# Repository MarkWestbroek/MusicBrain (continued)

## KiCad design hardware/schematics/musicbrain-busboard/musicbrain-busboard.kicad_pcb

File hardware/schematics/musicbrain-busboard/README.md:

# MusicBrain busboard — Teensy 4.1-backplane (rev 3.1, gen 2)

**Praktisch:** dit is de ruggengraat van het systeem. Eén Teensy 4.1
bestuurt alle functiekaarten die je in de zes slots prikt; het bord
verzorgt voeding, de SPI-bus, MIDI (2 in / 2 uit), USB-host, CAN, het
display en de gedeelde audio-lijnen. Hier begint elke MusicBrain-bouw.

**Status**: rev 3.1 AF — ERC 0, netlijst pad-voor-pad geverifieerd, **DRC 0/0**;
koper volledig via de freerouting-pijplijn (`--route-gnd`). Fab-pakket in
`fab/`. **Bestelbaar.**
**Plannen**: `doc/busboard-v3-plan.md` (v3-delta's) + `doc/busboard-v2-plan.md`
(architectuur/pintabellen) + `doc/spi-bus-spec.md` v2.0 (leidend voor de bus).

## Wat is v3 (gen 2)

- **Bord 203,2 × 128,5 mm (40 HP × 3U-paneelvlak)** — paneel, fronts en
  grondbord delen één footprint en gatenraster (M3: 4 hoeken + noord/zuid-
  midden) → zelfstandige unit mogelijk.
- **6 slots 2×12** (was 2×10), gecentreerd op het bordhart, steek 20,32 mm
  (4 HP). Slot-pinout per spi-bus-spec v2.0: pin 19 = CONVST, 20 = GND-guard,
  21–24 = MCLK/BCLK/LRCLK/I2SD·slot.
- **Audio over de bus**: klokrails gedeeld (zelfde netten als Teensy-I2S1 en
  de codec-header — klokmaster is een firmwarekeuze), één datalijn per slot.
- **J24 audiohub** (2×7, oostrand naast de hubs, búiten het kaartvolume):
  klokken + I2SD1–6 verzameld voor een toekomstige FPGA-/TDM-mixer; een
  expander-segment krijgt zijn klokken via zijn eigen J24 aangeleverd.
- **MIDI 2× IN / 2× UIT**: J22 (OUT2 = TX7/pin 29) met eigen 74LVC1G17 (U14).
- **J23 USB-host-doorvoer** (2×5): rij A = kabeltje van de Teensy-hostpads,
  rij B = kabeltje naar de paneel-USB-A; pin-voor-pin doorverbonden en
  volgorde-ongevoelig. VBUS loopt via VIN = de +5V-rail → daarom U2 nu
  **R-78E5.0-1.0** (1 A).
- **J25 Axon-voeding** (1×2, rev 3.1): +5V/GND naast J19, voedt de
  Axon-netbridge (ESP32-sidecar aan DLG1 — `doc/axon-plan.md`). Pin 1
  landt op het +5V-spoor van de voedingsbundel.

## Blokken (architectuur = v2)

- **Teensy 4.1** (west, op 2× 1×24 socketstrip; SMD ≤ 6 mm eronder mag).
- **6 slots** (J1–J6, 2×12) + **2 hubs** (J7/J8, 2×5 IDC, pinout = v1).
- **74HC154-CS-decoder** (U4, noordstrook): CSA0–3 + /E → 16 geografische CS.
- **IRQ-keten**: 2× 74HC165 (U5 zuidwest: IRQ1–6; U6 noordoost: IRQ7–12,
  uitlezen via decoder-Y14/IRQSTAT; per chip een PL-RC).
- **Expansie**: 74LVC245-buffer (U8) + J21 (2×13 IDC) voor één
  expander-segment (CS9–14, IRQ7–12; XRST-lijn = reserve sinds gen 2).
- **MIDI**: 2× IN (H11L1-opto's U9/U10) + 2× UIT (74LVC1G17 U11/U14).
- **CAN3**: SN65HVD230 (U12, zuidoost) + JP1-terminator + J16 (+12V mee).
- **Codec-poort** (J17, 2×7): I2S1 + CODEC_RST; I²C via de Qwiic-keten (J12).
- **TUNE-IN** (J18 + klem/deler → pin 1), **DLG-UART's** (J19/J20, Serial3/4).
- Voeding: J9 (2×5 IDC, 10-pins Eurorack: alleen ±12V/GND) → R-78E5.0-1.0
  (U2) → 5 V; AMS1117 (U3) → 3V3; ontkoppelbank C1–C8.

## Werkwijze koper

`gen_bus3_sch.py` + `gen_bus3_pcb.py` (placement + SES native inlezen).
Pijplijn: DSN-export via de KiCad-MCP-server → `prep_dsn.py --route-gnd`
(GND blijft routeerbaar net: de router respecteert dan de GND-pads én maakt
het net zelf af; de kopervlakken zijn bonus) → Docker-freerouting best-of-N →
netcheck + DRC 0/0 als poortwachters. `BUS3_NOROUTE=1` geeft het kale
placement-bord voor de DSN-export.

## Aansluitoverzicht

### Pinouts

Bovenaanzicht van het bord (kijkend op de pinnen); pin 1 = vierkant.
Gegenereerd uit het bordbestand met `hardware/kicad-generators/pinout_svg.py`.

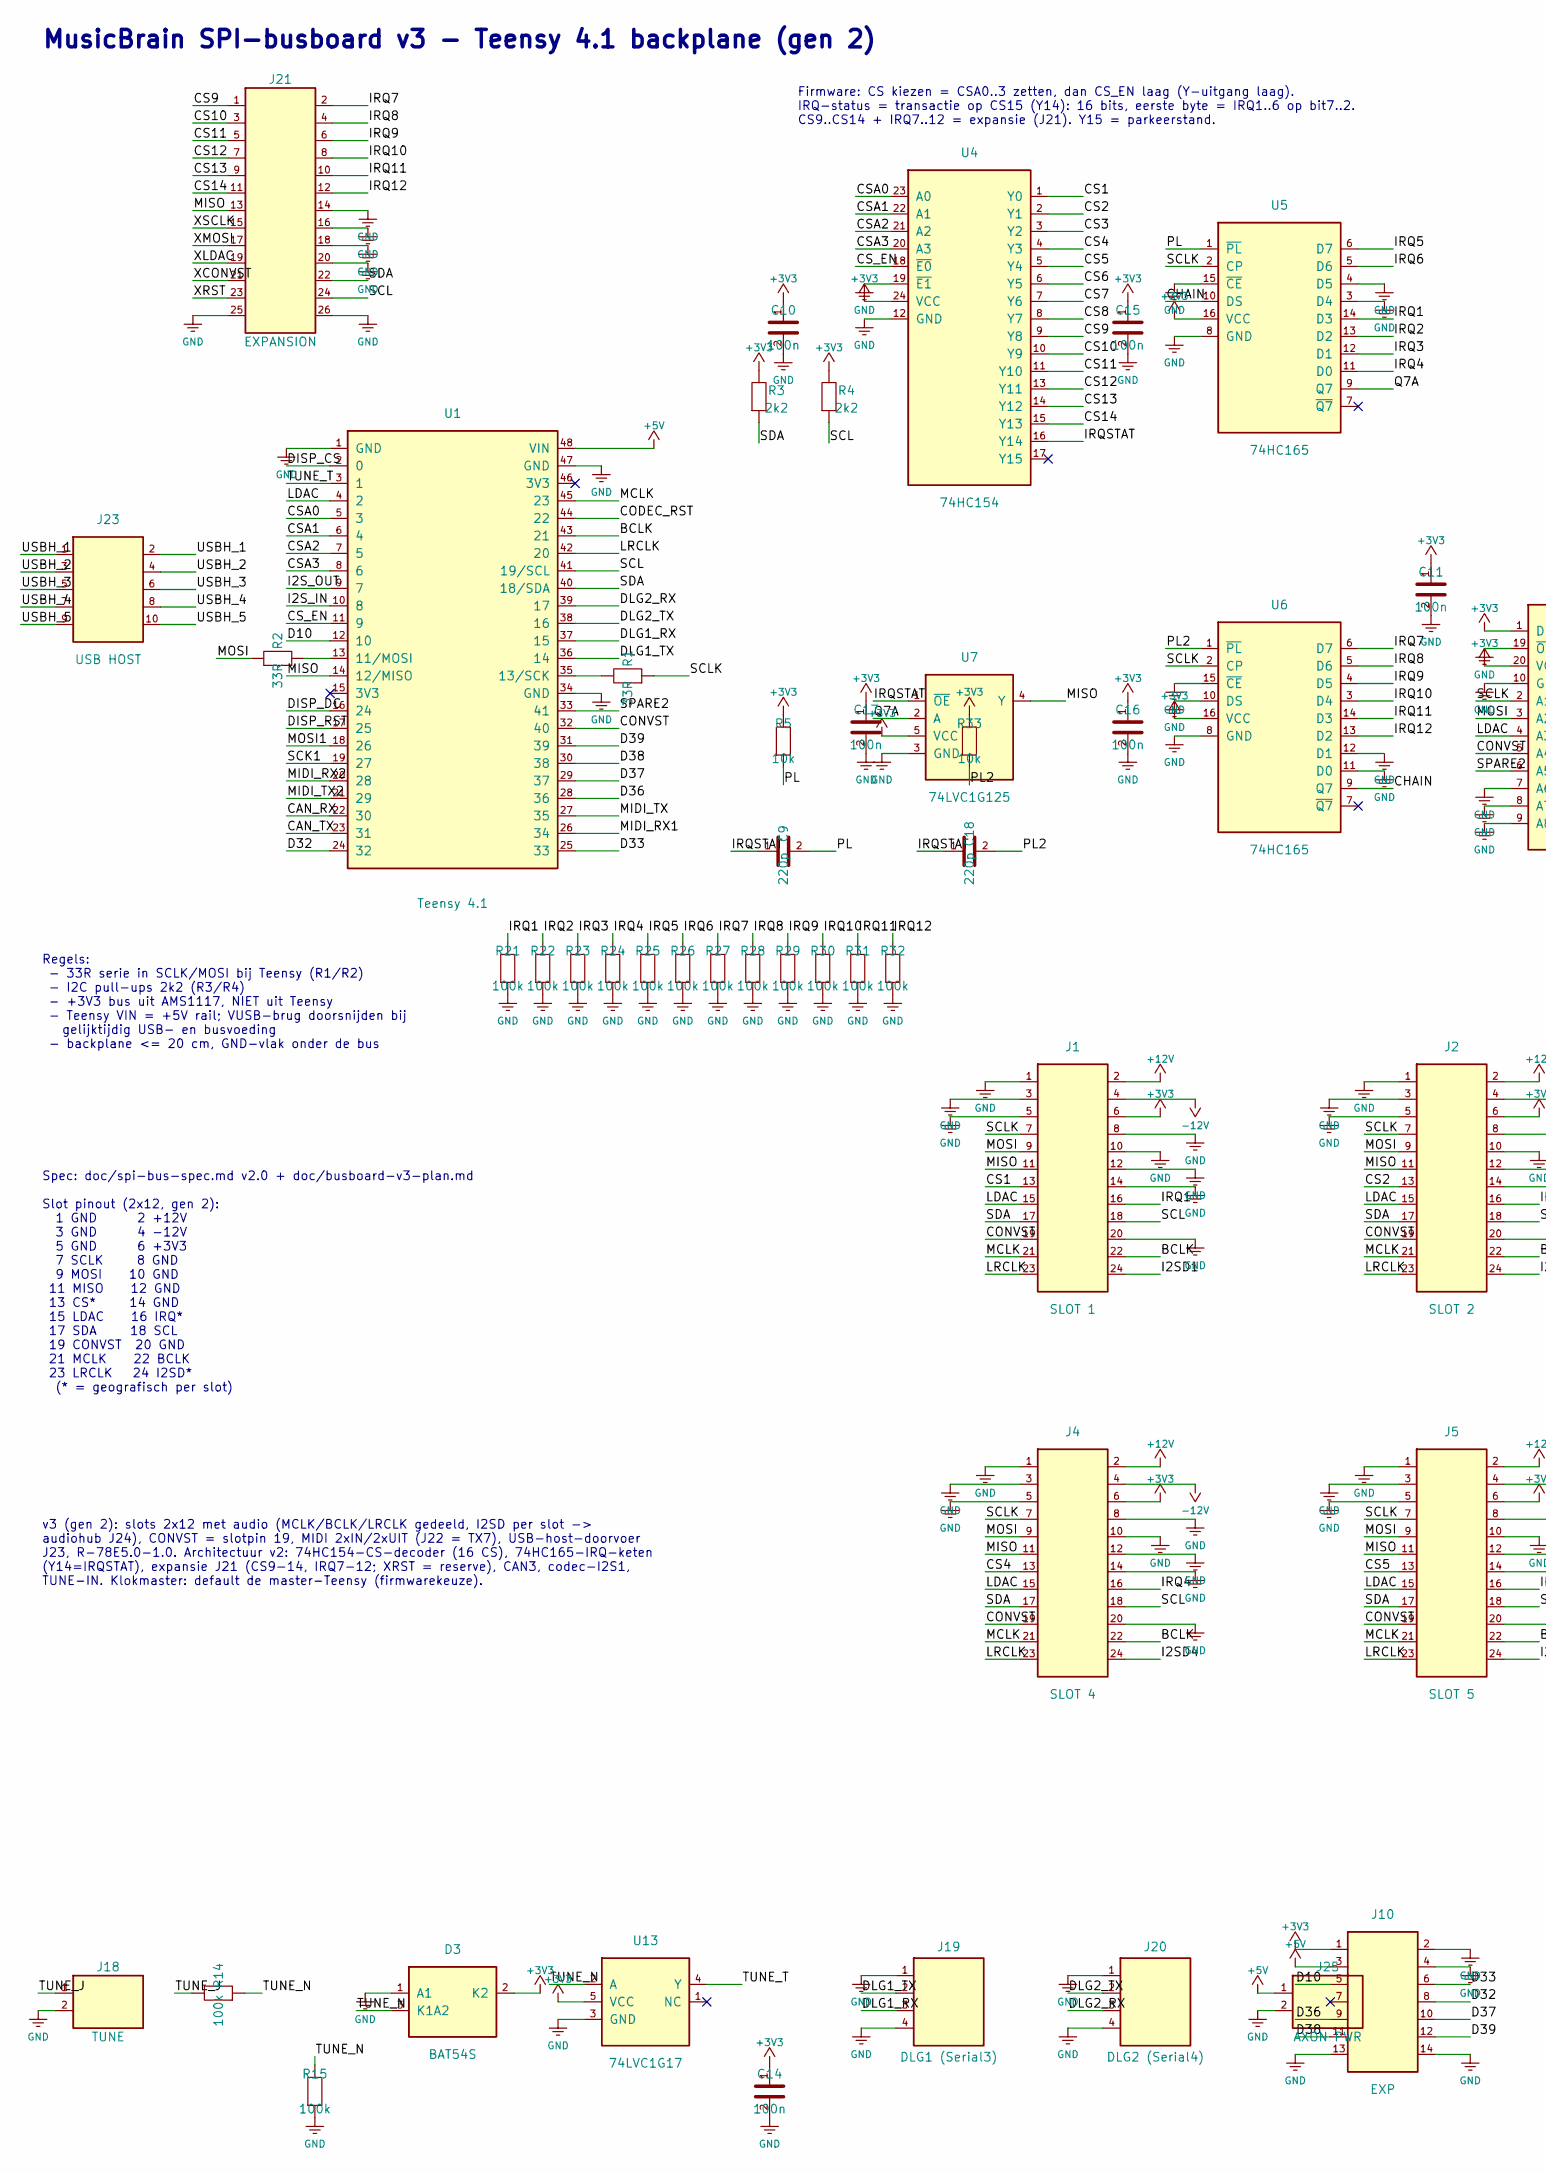
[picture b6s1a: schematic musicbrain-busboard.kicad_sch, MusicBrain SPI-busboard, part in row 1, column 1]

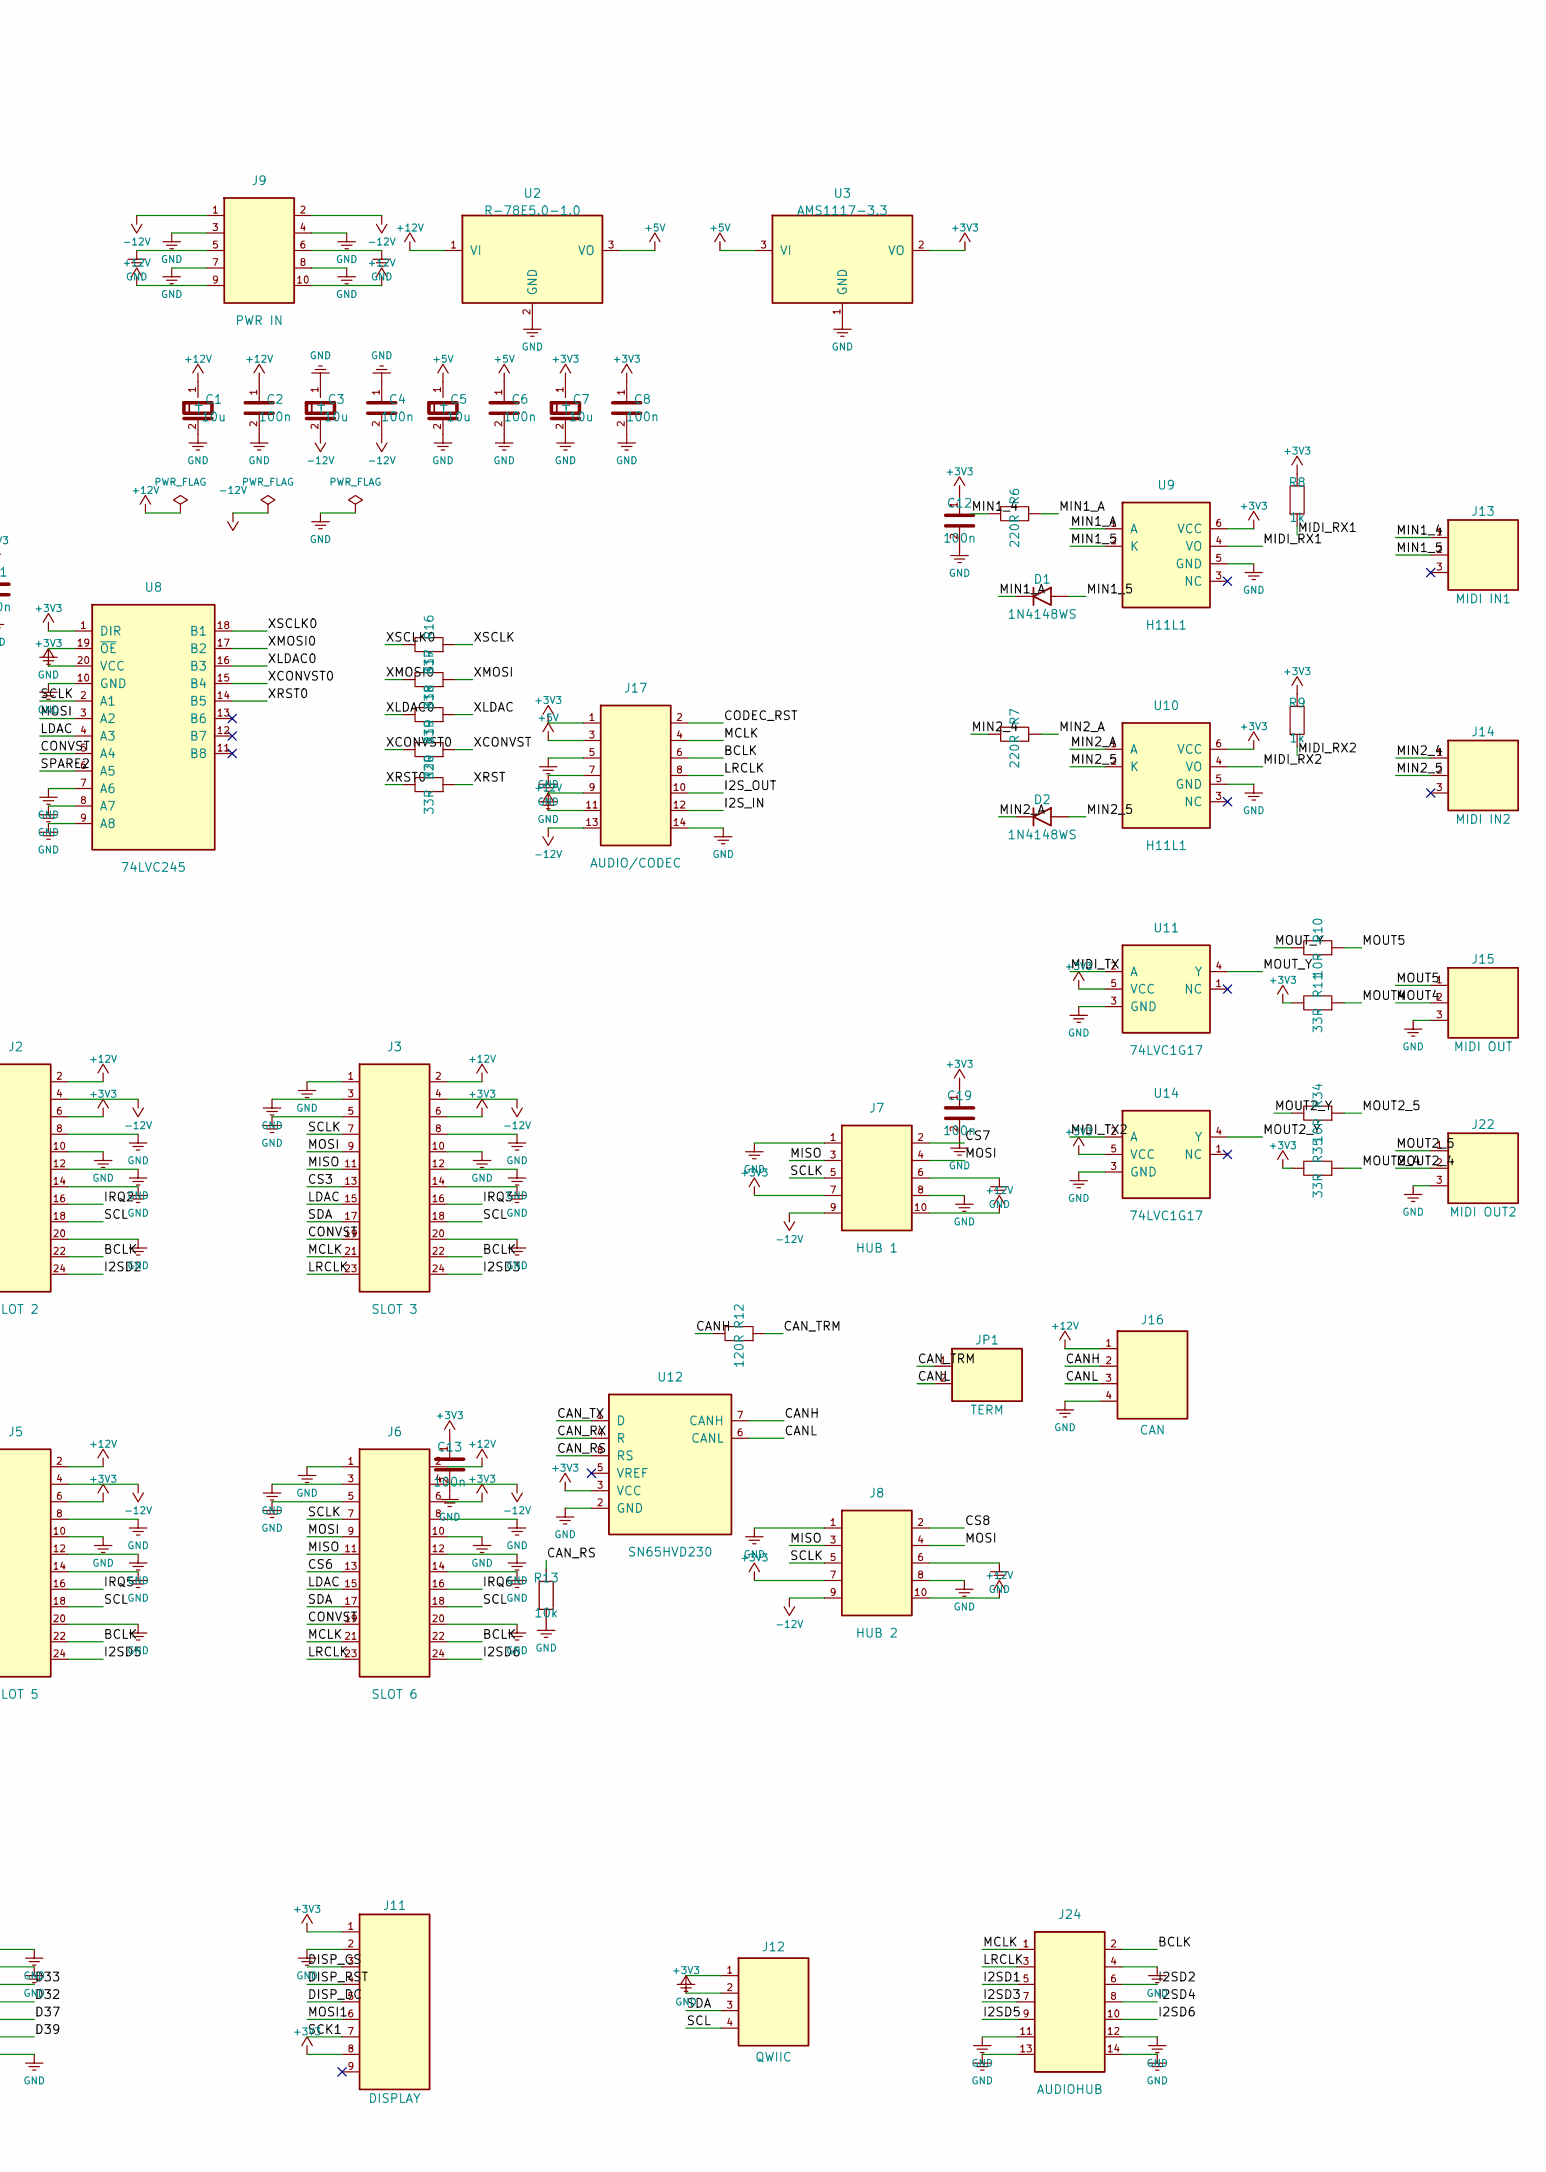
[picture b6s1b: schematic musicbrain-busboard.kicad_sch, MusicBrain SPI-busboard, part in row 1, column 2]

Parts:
C1, C3, C5, C7: 10u; CP_Elec_4x5.3
C2, C4, C6, C8, C10, C11, C12, C13, C14, C15, C16, C17, C19: 100n; C_0805_2012Metric
C9, C18: 220p; C_0805_2012Metric
D1, D2: 1N4148WS; D_SOD-323
D3: BAT54S; SOT-23
J1: SLOT 1; PinSocket_2x12_P2.54mm_Vertical
J2: SLOT 2; PinSocket_2x12_P2.54mm_Vertical
J3: SLOT 3; PinSocket_2x12_P2.54mm_Vertical
J4: SLOT 4; PinSocket_2x12_P2.54mm_Vertical
J5: SLOT 5; PinSocket_2x12_P2.54mm_Vertical
J6: SLOT 6; PinSocket_2x12_P2.54mm_Vertical
J7: HUB 1; IDC-Header_2x05_P2.54mm_Vertical
J8: HUB 2; IDC-Header_2x05_P2.54mm_Vertical
J9: PWR IN; IDC-Header_2x05_P2.54mm_Vertical
J10: EXP; PinHeader_2x07_P2.54mm_Vertical
J11: DISPLAY; PinHeader_1x09_P2.54mm_Vertical
J12: QWIIC; PinHeader_1x04_P2.54mm_Vertical
J13: MIDI IN1; PinHeader_1x03_P2.54mm_Vertical
J14: MIDI IN2; PinHeader_1x03_P2.54mm_Vertical
J15: MIDI OUT; PinHeader_1x03_P2.54mm_Vertical
J16: CAN; PinHeader_1x04_P2.54mm_Vertical
J17: AUDIO/CODEC; PinHeader_2x07_P2.54mm_Vertical
J18: TUNE; PinHeader_1x02_P2.54mm_Vertical
J19: DLG1 (Serial3); PinHeader_1x04_P2.54mm_Vertical
J20: DLG2 (Serial4); PinHeader_1x04_P2.54mm_Vertical
J21: EXPANSION; IDC-Header_2x13_P2.54mm_Vertical
J22: MIDI OUT2; PinHeader_1x03_P2.54mm_Vertical
J23: USB HOST; PinHeader_2x05_P2.54mm_Vertical
J24: AUDIOHUB; PinHeader_2x07_P2.54mm_Vertical
J25: AXON PWR; PinHeader_1x02_P2.54mm_Vertical
JP1: TERM; SolderJumper-2_P1.3mm_Open_TrianglePad1.0x1.5mm
R1, R2, R11, R16, R17, R18, R19, R20, R35: 33R; R_0805_2012Metric
R3, R4: 2k2; R_0805_2012Metric
R5, R13, R33: 10k; R_0805_2012Metric
R6, R7: 220R; R_0805_2012Metric
R8, R9: 1k; R_0805_2012Metric
R10, R34: 10R; R_0805_2012Metric
R12: 120R; R_0805_2012Metric
R14, R15, R21, R22, R23, R24, R25, R26, R27, R28, R29, R30, R31, R32: 100k; R_0805_2012Metric
U1: Teensy 4.1
U2: R-78E5.0-1.0; Converter_DCDC_RECOM_R-78E-0.5_THT
U3: AMS1117-3.3; SOT-223-3_TabPin2
U4: 74HC154; SOIC-24W_7.5x15.4mm_P1.27mm
U5, U6: 74HC165; SOIC-16_3.9x9.9mm_P1.27mm
U7: 74LVC1G125; SOT-23-5
U8: 74LVC245; SOIC-20W_7.5x12.8mm_P1.27mm
U9, U10: H11L1; DIP-6_W7.62mm
U11, U13, U14: 74LVC1G17; SOT-23-5
U12: SN65HVD230; SOIC-8_3.9x4.9mm_P1.27mm

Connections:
+3V3: C7.1 (+), C8.1, C10.1, C11.1, C12.1, C13.1, C14.1, C15.1, C16.1, C17.1, C19.1, D3.2 (K2), J1.6, J2.6, J3.6, J4.6, J5.6, J6.6, J7.7, J8.7, J10.1, J11.1, J11.8, J12.2, J17.1, R3.1, R4.1, R5.1, R8.1, R9.1, R11.1, R33.1, R35.1, U3.2 (VO), U4.24 (VCC), U5.16 (VCC), U6.16 (VCC), U7.5 (VCC), U8.1 (DIR), U8.20 (VCC), U9.6 (VCC), U10.6 (VCC), U11.5 (VCC), U12.3 (VCC), U13.5 (VCC), U14.5 (VCC)
+5V: C5.1 (+), C6.1, J10.3, J17.3, J25.1, U1.48 (VIN), U2.3 (VO), U3.3 (VI)
+12V: C1.1 (+), C2.1, J1.2, J2.2, J3.2, J4.2, J5.2, J6.2, J7.10, J8.10, J9.9, J9.10, J16.1, J17.11, U2.1 (VI)
-12V: C3.2 (-), C4.2, J1.4, J2.4, J3.4, J4.4, J5.4, J6.4, J7.9, J8.9, J9.1, J9.2, J17.13
/BCLK: J1.22, J2.22, J3.22, J4.22, J5.22, J6.22, J17.6, J24.2, U1.43 (21)
/CANH: J16.2, R12.1, U12.7 (CANH)
/CANL: J16.3, JP1.2, U12.6 (CANL)
/CAN_RS: R13.1, U12.8 (RS)
/CAN_RX: U1.22 (30), U12.4 (R)
/CAN_TRM: JP1.1, R12.2
/CAN_TX: U1.23 (31), U12.1 (D)
/CHAIN: U5.10 (DS), U6.9 (Q7)
/CODEC_RST: J17.2, U1.44 (22)
/CONVST: J1.19, J2.19, J3.19, J4.19, J5.19, J6.19, U1.32 (40), U8.5 (A4)
/CS1: J1.13, U4.1 (Y0)
/CS2: J2.13, U4.2 (Y1)
/CS3: J3.13, U4.3 (Y2)
/CS4: J4.13, U4.4 (Y3)
/CS5: J5.13, U4.5 (Y4)
/CS6: J6.13, U4.6 (Y5)
/CS7: J7.2, U4.7 (Y6)
/CS8: J8.2, U4.8 (Y7)
/CS9: J21.1, U4.9 (Y8)
/CS10: J21.3, U4.10 (Y9)
/CS11: J21.5, U4.11 (Y10)
/CS12: J21.7, U4.13 (Y11)
/CS13: J21.9, U4.14 (Y12)
/CS14: J21.11, U4.15 (Y13)
/CSA0: U1.5 (3), U4.23 (A0)
/CSA1: U1.6 (4), U4.22 (A1)
/CSA2: U1.7 (5), U4.21 (A2)
/CSA3: U1.8 (6), U4.20 (A3)
/CS_EN: U1.11 (9), U4.18 (~E0)
/D10: J10.5, U1.12 (10)
/D32: J10.8, U1.24 (32)
/D33: J10.6, U1.25 (33)
/D36: J10.9, U1.28 (36)
/D37: J10.10, U1.29 (37)
/D38: J10.11, U1.30 (38)
/D39: J10.12, U1.31 (39)
/DISP_CS: J11.3, U1.2 (0)
/DISP_DC: J11.5, U1.16 (24)
/DISP_RST: J11.4, U1.17 (25)
/DLG1_RX: J19.3, U1.37 (15)
/DLG1_TX: J19.2, U1.36 (14)
/DLG2_RX: J20.3, U1.39 (17)
/DLG2_TX: J20.2, U1.38 (16)
/I2SD1: J1.24, J24.5
/I2SD2: J2.24, J24.6
/I2SD3: J3.24, J24.7
/I2SD4: J4.24, J24.8
/I2SD5: J5.24, J24.9
/I2SD6: J6.24, J24.10
/I2S_IN: J17.12, U1.10 (8)
/I2S_OUT: J17.10, U1.9 (7)
/IRQ1: J1.16, R21.1, U5.14 (D3)
/IRQ2: J2.16, R22.1, U5.13 (D2)
/IRQ3: J3.16, R23.1, U5.12 (D1)
/IRQ4: J4.16, R24.1, U5.11 (D0)
/IRQ5: J5.16, R25.1, U5.6 (D7)
/IRQ6: J6.16, R26.1, U5.5 (D6)
/IRQ7: J21.2, R27.1, U6.6 (D7)
/IRQ8: J21.4, R28.1, U6.5 (D6)
/IRQ9: J21.6, R29.1, U6.4 (D5)
/IRQ10: J21.8, R30.1, U6.3 (D4)
/IRQ11: J21.10, R31.1, U6.14 (D3)
/IRQ12: J21.12, R32.1, U6.13 (D2)
/IRQSTAT: C9.1, C18.1, U4.16 (Y14), U7.1 (~OE)
/LDAC: J1.15, J2.15, J3.15, J4.15, J5.15, J6.15, U1.4 (2), U8.4 (A3)
/LRCLK: J1.23, J2.23, J3.23, J4.23, J5.23, J6.23, J17.8, J24.3, U1.42 (20)
/MCLK: J1.21, J2.21, J3.21, J4.21, J5.21, J6.21, J17.4, J24.1, U1.45 (23)
/MIDI_RX1: R8.2, U1.26 (34), U9.4 (VO)
/MIDI_RX2: R9.2, U1.20 (28), U10.4 (VO)
/MIDI_TX: U1.27 (35), U11.2 (A)
/MIDI_TX2: U1.21 (29), U14.2 (A)
/MIN1_4: J13.1, R6.1
/MIN1_5: D1.2 (A), J13.2, U9.2 (K)
/MIN1_A: D1.1 (K), R6.2, U9.1 (A)
/MIN2_4: J14.1, R7.1
/MIN2_5: D2.2 (A), J14.2, U10.2 (K)
/MIN2_A: D2.1 (K), R7.2, U10.1 (A)
/MISO: J1.11, J2.11, J3.11, J4.11, J5.11, J6.11, J7.3, J8.3, J21.13, U1.14 (12/MISO), U7.4 (Y)
/MOSI: J1.9, J2.9, J3.9, J4.9, J5.9, J6.9, J7.4, J8.4, R2.1, U8.3 (A2)
/MOSI1: J11.6, U1.18 (26)
/MOUT2_4: J22.2, R35.2
/MOUT2_5: J22.1, R34.2
/MOUT2_Y: R34.1, U14.4 (Y)
/MOUT4: J15.2, R11.2
/MOUT5: J15.1, R10.2
/MOUT_Y: R10.1, U11.4 (Y)
/PL: C9.2, R5.2, U5.1 (~PL)
/PL2: C18.2, R33.2, U6.1 (~PL)
/Q7A: U5.9 (Q7), U7.2 (A)
/SCK1: J11.7, U1.19 (27)
/SCL: J1.18, J2.18, J3.18, J4.18, J5.18, J6.18, J12.4, J21.24, R4.2, U1.41 (19/SCL)
/SCLK: J1.7, J2.7, J3.7, J4.7, J5.7, J6.7, J7.5, J8.5, R1.2, U5.2 (CP), U6.2 (CP), U8.2 (A1)
/SDA: J1.17, J2.17, J3.17, J4.17, J5.17, J6.17, J12.3, J21.22, R3.2, U1.40 (18/SDA)
/SPARE2: U1.33 (41), U8.6 (A5)
/TUNE_J: J18.1, R14.1
/TUNE_N: D3.3 (K1A2), R14.2, R15.1, U13.2 (A)
/TUNE_T: U1.3 (1), U13.4 (Y)
/USBH_1: J23.1, J23.2
/USBH_2: J23.3, J23.4
/USBH_3: J23.5, J23.6
/USBH_4: J23.7, J23.8
/USBH_5: J23.9, J23.10
/XCONVST: J21.21, R19.2
/XCONVST0: R19.1, U8.15 (B4)
/XLDAC: J21.19, R18.2
/XLDAC0: R18.1, U8.16 (B3)
/XMOSI: J21.17, R17.2
/XMOSI0: R17.1, U8.17 (B2)
/XRST: J21.23, R20.2
/XRST0: R20.1, U8.14 (B5)
/XSCLK: J21.15, R16.2
/XSCLK0: R16.1, U8.18 (B1)
GND: C1.2 (-), C2.2, C3.1 (+), C4.1, C5.2 (-), C6.2, C7.2 (-), C8.2, C10.2, C11.2, C12.2, C13.2, C14.2, C15.2, C16.2, C17.2, C19.2, D3.1 (A1), J1.1, J1.3, J1.5, J1.8, J1.10, J1.12, J1.14, J1.20, J2.1, J2.3, J2.5, J2.8, J2.10, J2.12, J2.14, J2.20, J3.1, J3.3, J3.5, J3.8, J3.10, J3.12, J3.14, J3.20, J4.1, J4.3, J4.5, J4.8, J4.10, J4.12, J4.14, J4.20, J5.1, J5.3, J5.5, J5.8, J5.10, J5.12, J5.14, J5.20, J6.1, J6.3, J6.5, J6.8, J6.10, J6.12, J6.14, J6.20, J7.1, J7.6, J7.8, J8.1, J8.6, J8.8, J9.3, J9.4, J9.5, J9.6, J9.7, J9.8, J10.2, J10.4, J10.13, J10.14, J11.2, J12.1, J15.3, J16.4, J17.5, J17.7, J17.9, J17.14, J18.2, J19.1, J19.4, J20.1, J20.4, J21.14, J21.16, J21.18, J21.20, J21.25, J21.26, J22.3, J24.4, J24.11, J24.12, J24.13, J24.14, J25.2, R13.2, R15.2, R21.2, R22.2, R23.2, R24.2, R25.2, R26.2, R27.2, R28.2, R29.2, R30.2, R31.2, R32.2, U1.1 (GND), U1.34 (GND), U1.47 (GND), U2.2 (GND), U3.1 (GND), U4.12 (GND), U4.19 (~E1), U5.3 (D4), U5.4 (D5), U5.8 (GND), U5.15 (~CE), U6.8 (GND), U6.10 (DS), U6.11 (D0), U6.12 (D1), U6.15 (~CE), U7.3 (GND), U8.7 (A6), U8.8 (A7), U8.9 (A8), U8.10 (GND), U8.19 (~OE), U9.5 (GND), U10.5 (GND), U11.3 (GND), U12.2 (GND), U13.3 (GND), U14.3 (GND)
unnamed: R2.2, U1.13 (11/MOSI)
unnamed: R1.1, U1.35 (13/SCK)

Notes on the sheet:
MusicBrain SPI-busboard v3 - Teensy 4.1 backplane (gen 2)
v3 (gen 2): slots 2x12 met audio (MCLK/BCLK/LRCLK gedeeld, I2SD per slot -> audiohub J24), CONVST = slotpin 19, MIDI 2xIN/2xUIT (J22 = TX7), USB-host-doorvoer J23, R-78E5.0-1.0. Architectuur v2: 74HC154-CS-decoder (16 CS), 74HC165-IRQ-keten (Y14=IRQSTAT), expansie J21 (CS9-14, IRQ7-12; XRST = reser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
Spec: doc/spi-bus-spec.md v2.0 + doc/busboard-v3-plan.md Slot pinout (2x12, gen 2): 1 GND 2 +12V 3 GND 4 -12V 5 GND 6 +3V3 7 SCLK 8 GND 9 MOSI 10 GND 11 MISO 12 GND 13 CS* 14 GND 15 LDAC 16 IRQ* 17 SDA 18 SCL 19 CONVST 20 GND 21 MCLK 22 BCLK 23 LRCLK 24 I2SD* (* = geografisch per slot)
Regels: - 33R serie in SCLK/MOSI bij Teensy (R1/R2) - I2C pull-ups 2k2 (R3/R4) - +3V3 bus uit AMS1117, NIET uit Teensy - Teensy VIN = +5V rail; VUSB-brug doorsnijden bij gelijktijdig USB- en busvoeding - backplane <= 20 cm, GND-vlak onder de bus
Firmware: CS kiezen = CSA0..3 zetten, dan CS_EN laag (Y-uitgang laag). IRQ-status = transactie op CS15 (Y14): 16 bits, eerste byte = IRQ1..6 op bit7..2. CS9..CS14 + IRQ7..12 = expansie (J21). Y15 = parkeerstand.

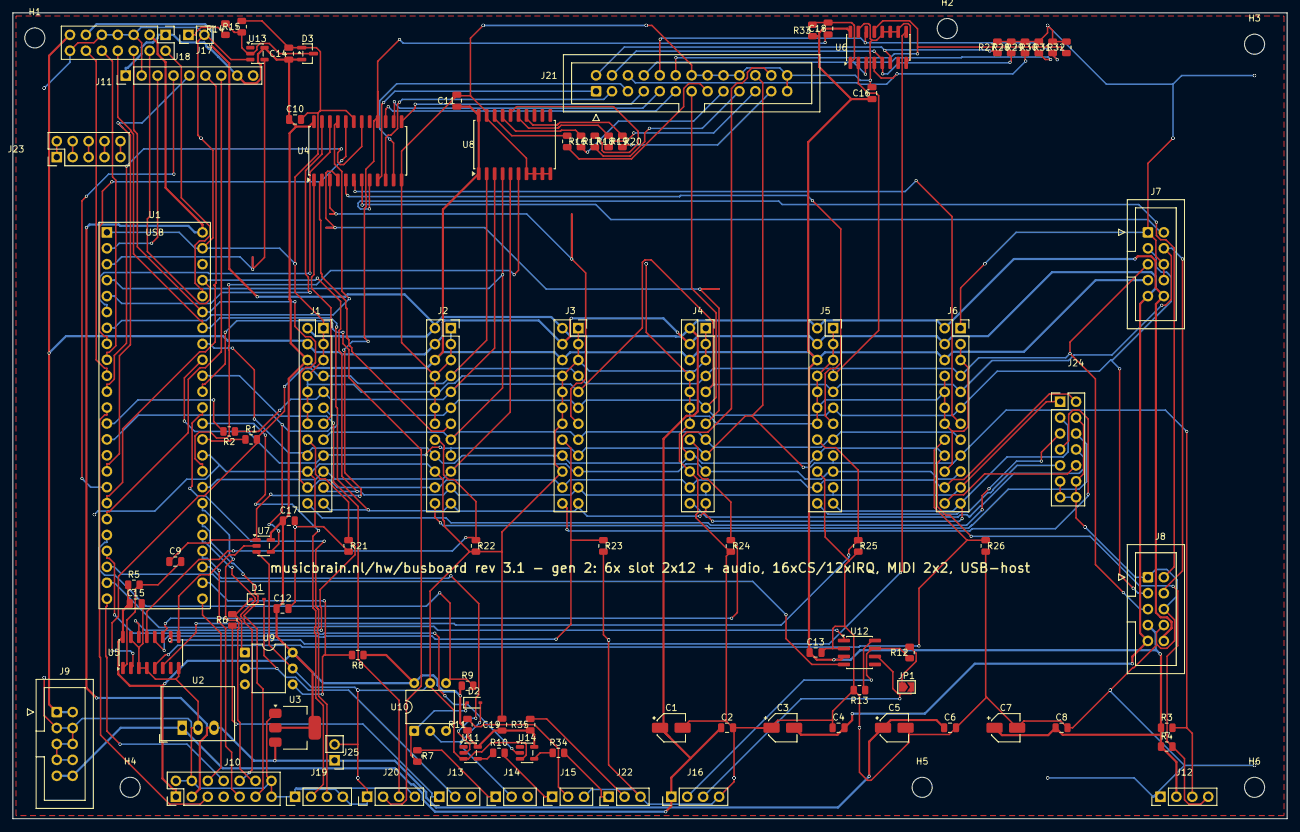
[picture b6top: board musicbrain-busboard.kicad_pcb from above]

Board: 2 copper layers, 203.2 x 128.5 mm, 103 parts (0 on the bottom side), 119 nets.

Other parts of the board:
H1, H2, H3, H4, H5, H6: M3; MountingHole_3.2mm_M3

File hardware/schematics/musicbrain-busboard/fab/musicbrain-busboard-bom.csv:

"Comment","Designator","Footprint","LCSC Part #"
"10u","C1,C3,C5,C7","CP_Elec_4x5.3","C3343"
"100n","C2,C4,C6,C8,C10,C11,C12,C13,C14,C15,C16,C17,C19","C_0805_2012Metric","C49678"
"220p","C9,C18","C_0805_2012Metric","C107145"
"1N4148WS","D1,D2","D_SOD-323","C2128"
"BAT54S","D3","SOT-23","C7420333"
"SLOT 1","J1","PinSocket_2x12_P2.54mm_Vertical",""
"SLOT 2","J2","PinSocket_2x12_P2.54mm_Vertical",""
"SLOT 3","J3","PinSocket_2x12_P2.54mm_Vertical",""
"SLOT 4","J4","PinSocket_2x12_P2.54mm_Vertical",""
"SLOT 5","J5","PinSocket_2x12_P2.54mm_Vertical",""
"SLOT 6","J6","PinSocket_2x12_P2.54mm_Vertical",""
"HUB 1","J7","IDC-Header_2x05_P2.54mm_Vertical","C5665"
"HUB 2","J8","IDC-Header_2x05_P2.54mm_Vertical","C5665"
"PWR IN","J9","IDC-Header_2x05_P2.54mm_Vertical","C5665"
"EXP","J10","PinHeader_2x07_P2.54mm_Vertical",""
"DISPLAY","J11","PinHeader_1x09_P2.54mm_Vertical",""
"QWIIC","J12","PinHeader_1x04_P2.54mm_Vertical",""
"MIDI IN1","J13","PinHeader_1x03_P2.54mm_Vertical",""
"MIDI IN2","J14","PinHeader_1x03_P2.54mm_Vertical",""
"MIDI OUT","J15","PinHeader_1x03_P2.54mm_Vertical",""
"CAN","J16","PinHeader_1x04_P2.54mm_Vertical",""
"AUDIO/CODEC","J17","PinHeader_2x07_P2.54mm_Vertical",""
"TUNE","J18","PinHeader_1x02_P2.54mm_Vertical",""
"DLG1 (Serial3)","J19","PinHeader_1x04_P2.54mm_Vertical",""
"DLG2 (Serial4)","J20","PinHeader_1x04_P2.54mm_Vertical",""
"EXPANSION","J21","IDC-Header_2x13_P2.54mm_Vertical","C2884553"
"MIDI OUT2","J22","PinHeader_1x03_P2.54mm_Vertical",""
"USB HOST","J23","PinHeader_2x05_P2.54mm_Vertical",""
"AUDIOHUB","J24","PinHeader_2x07_P2.54mm_Vertical",""
"AXON PWR","J25","PinHeader_1x02_P2.54mm_Vertical",""
"TERM","JP1","SolderJumper-2_P1.3mm_Open_TrianglePad1.0x1.5mm",""
"33R","R1,R2,R11,R16,R17,R18,R19,R20,R35","R_0805_2012Metric","C17634"
"2k2","R3,R4","R_0805_2012Metric","C17520"
"10k","R5,R13,R33","R_0805_2012Metric","C17414"
"220R","R6,R7","R_0805_2012Metric","C17557"
"1k","R8,R9","R_0805_2012Metric","C17513"
"10R","R10,R34","R_0805_2012Metric","C17415"
"120R","R12","R_0805_2012Metric","C17437"
"100k","R14,R15,R21,R22,R23,R24,R25,R26,R27,R28,R29,R30,R31,R32","R_0805_2012Metric","C149504"
"Teensy 4.1","U1","",""
"R-78E5.0-1.0","U2","Converter_DCDC_RECOM_R-78E-0.5_THT",""
"AMS1117-3.3","U3","SOT-223-3_TabPin2","C6186"
"74HC154","U4","SOIC-24W_7.5x15.4mm_P1.27mm","C2832236"
"74HC165","U5,U6","SOIC-16_3.9x9.9mm_P1.27mm","C5613"
"74LVC1G125","U7","SOT-23-5","C12518"
"74LVC245","U8","SOIC-20W_7.5x12.8mm_P1.27mm","C6080"
"H11L1","U9,U10","DIP-6_W7.62mm",""
"74LVC1G17","U11,U13,U14","SOT-23-5","C19829593"
"SN65HVD230","U12","SOIC-8_3.9x4.9mm_P1.27mm","C12084"

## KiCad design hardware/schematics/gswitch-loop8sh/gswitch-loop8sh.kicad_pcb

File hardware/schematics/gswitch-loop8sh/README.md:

# gswitch-loop8sh — 8× true-bypass relaisloop, klem-variant (Sander van Herk)

**Status**: rev 0.1 geroute — ERC 0, netcheck OK, DRC 0/0 (2026-07-16).
**Nog niet bestellen**: eerst LCSC-matching/fab-pakket maken
(`jlc_fix.py`, zie order-recept) en klemmen-type bevestigen.
Leidende spec: [`doc/guitar-switcher-spec.md`](../../../doc/guitar-switcher-spec.md).

*(Regenereren: `python hardware/kicad-generators/board_overview.py
<pcb> gswitch-loop8sh-overzicht.json`.)*

## Wat dit bord is

De compacte variant van [gswitch-loop8](../gswitch-loop8/): zelfde
schakeling (8 DPDT-relaisloops, bypass op NC, RJ45-keten, 595 + ULN2803A),
maar de acht ACJS-MHD-stapeljacks zijn vervangen door **3-polige
schroefklemmen** — de klant soldeert/klemt zijn eigen kabels. Audio-IN/UIT
(J7/J8, ACJS-MH), RJ45 chain in/thru en de doorlink-voorzieningen blijven.

- Bord: **150 × 44 mm**, 2 laags (loop8: 200 × 58). Klemmen/jacks/RJ45's
  THT, rest SMD (JLC-assemblage).
- AGND en GND gescheiden zones (audio noord, besturing zuid); koppeling
  alleen via JP3 (AGND=CHASSIS) en de hybride RC C7/R33 (GND=CHASSIS).
- Bitvolgorde firmware identiek aan loop8: D1 (bit 0) = loop 1 …
  D8 (bit 7) = loop 8; oostgroep ULN-toewijzing geografisch gespiegeld
  (`OUTPIN` in de generator).

## ⚠️ Geen normalling op de klemmen

De stapeljack van loop8 heeft een verbreekcontact dat een **lege loop
automatisch doorlust**. Een schroefklem heeft dat niet: een geactiveerde
loop zonder aangesloten effect breekt het signaalpad. Regels:

- Lege loop **nooit activeren** (relais uit = NC = bypass, signaal loopt
  gewoon door) — in de firmware/brain de ongebruikte loops uitvinken.
- Of: SEND en RETURN van de lege klem doorlussen met een draadbruggetje.

## Klem-pinout (J11–J18, steek 3,5 mm)

| klem-pin | 1 (west) | 2 | 3 (oost) |
|---|---|---|---|
| functie | **SEND** (naar effect-in) | AGND (kabelscherm) | **RETURN** (van effect-uit) |

## Overige connectoren

**J1 — chain IN (RJ45, van de brain) / J2 — chain THRU.** ⚠️ Géén
ethernet: pin 4 voert 12 V! J3/J4 = zelfde signalen als 2×4-header
(interne doorlink); RJ45-schermen → CHASSIS.

| pin | 1 | 2 | 3 | 4 | 5 | 6 | 7 | 8 |
|---|---|---|---|---|---|---|---|---|
| functie | CLK | GND | DATA | **+12V** | GND | DRET (terug) | LATCH | EN |

**J7 audio IN / J8 audio UIT (ACJS-MH):** tip = signaal, ring/sleeve →
AGND; J7-tip-verbreek → JP2 (mute lege ingang). **J5/J6** = dezelfde
audio als soldeerpads (pin 1 = signaal, pin 2 = AGND) voor de
doorlink naar een tweede bord.

Diagrammen van álle connectoren: [`pinouts/`](pinouts/)
(gegenereerd met `pinout_svg.py --alle`).

## Jumpers

| Jumper | Functie | Wanneer dicht |
|---|---|---|
| JP1 TERM | sluit DATA_RET-lus (SER → DRET) | alleen op het **laatste** bord in de keten |
| JP2 IN-TN=AGND | mute een lege IN-jack | dicht bij losse kastjes; **open** bij audio-doorlink via J5 |
| JP3 AGND=CHASSIS | sterpunt audio-massa → behuizing | standaard dicht (één per kastje!) |

## Onderdelen-notities

- **Relais**: TQ2SA-12V(-Z) — JLC **C2684447** (SMD, voorraad). Kleinere
  5V-relais (Omron G6K) winnen niets: de klemmenrij zet de 12 mm-steek,
  en 12 V-spoelen passen bij de bestaande keten/brain.
- **Klemmen**: Phoenix PT 1,5/3-3,5-H (3,5 mm steek, 3-polig, liggend).
  Alternatief met zelfde land-pattern kan; footprint uit KiCad-lib.
- **Jacks**: ACJS-MH (enkel), Mouser. ⚠️ eerste levering doorpiepen:
  zonder plug is T–TN gesloten.
- **RJ45**: zie loop8-README (Ninigi GE-familie; NPTH-posts checken).
- **BOM/LCSC**: symbolen hebben nog géén LCSC-veld — vóór fab-run
  `jlc_fix.py`-matching doen en false matches checken (order-recept).

## Bouwen

```
python hardware/kicad-generators/gen_gswitch_loop8sh.py  # sch + pcb (+ SES indien aanwezig)
kicad-cli sch erc --severity-error ... ; kicad-cli sch export netlist ... ; cardlib.netcheck(...)
kicad-cli pcb drc --severity-error --refill-zones ...
# routing: mcp export_dsn -> gswitch_dsn_prep.py --keepout-box=100.5,100.5,249.5,124.0
#   -> docker freerouting -> gswitch-loop8sh.ses -> generator opnieuw (bakt SES in)
# GND-eilanden: gnd_stitch.py (KiCad-python) -> gnd_stitch.json -> generator opnieuw
```

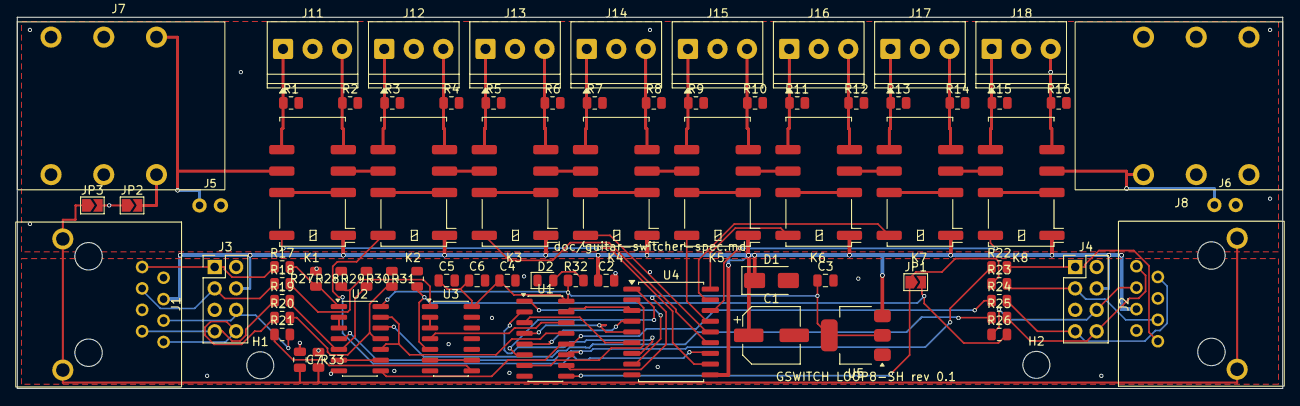
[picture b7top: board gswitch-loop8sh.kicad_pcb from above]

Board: 2 copper layers, 150.0 x 44.0 mm, 76 parts (0 on the bottom side), 82 nets.

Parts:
C1: 100u/25V; CP_Elec_6.3x7.7
C2, C4, C5, C6, C7: 100n; C_0805_2012Metric
C3: 10u; C_0805_2012Metric
D1: SMAJ15A; D_SMA
D2: LED-GN; LED_0805_2012Metric
H1, H2: M3; MH32
J1, J2: RJ45-S; RJ45_shielded
J3: CHAIN-LINK-IN; PinHeader_2x04_P2.54mm_Vertical
J4: CHAIN-LINK-UIT; PinHeader_2x04_P2.54mm_Vertical
J5: LINK-IN; LINK2
J6: LINK-UIT; LINK2
J7, J8: ACJS-MH; ACJS_MH
J11: LOOP1; TerminalBlock_Phoenix_PT-1,5-3-3.5-H_1x03_P3.50mm_Horizontal
J12: LOOP2; TerminalBlock_Phoenix_PT-1,5-3-3.5-H_1x03_P3.50mm_Horizontal
J13: LOOP3; TerminalBlock_Phoenix_PT-1,5-3-3.5-H_1x03_P3.50mm_Horizontal
J14: LOOP4; TerminalBlock_Phoenix_PT-1,5-3-3.5-H_1x03_P3.50mm_Horizontal
J15: LOOP5; TerminalBlock_Phoenix_PT-1,5-3-3.5-H_1x03_P3.50mm_Horizontal
J16: LOOP6; TerminalBlock_Phoenix_PT-1,5-3-3.5-H_1x03_P3.50mm_Horizontal
J17: LOOP7; TerminalBlock_Phoenix_PT-1,5-3-3.5-H_1x03_P3.50mm_Horizontal
J18: LOOP8; TerminalBlock_Phoenix_PT-1,5-3-3.5-H_1x03_P3.50mm_Horizontal
JP1: TERM; SolderJumper-2_P1.3mm_Open_TrianglePad1.0x1.5mm
JP2: IN-TN=AGND; SolderJumper-2_P1.3mm_Open_TrianglePad1.0x1.5mm
JP3: AGND=CHASSIS; SolderJumper-2_P1.3mm_Open_TrianglePad1.0x1.5mm
K1, K2, K3, K4, K5, K6, K7, K8: EE2-12NU/TQ2SA-12V; Relay_DPDT_Kemet_EE2_NU
R1, R2, R3, R4, R5, R6, R7, R8, R9, R10, R11, R12, R13, R14, R15, R16, R33: 1M; R_0805_2012Metric
R17, R18, R19, R20, R21, R22, R23, R24, R25, R26: 100R; R_0805_2012Metric
R27, R28, R29, R30, R31: 100k; R_0805_2012Metric
R32: 4k7; R_0805_2012Metric
U1: 74HC595; SOIC-16_3.9x9.9mm_P1.27mm
U2, U3: 74HC14; SOIC-14_3.9x8.7mm_P1.27mm
U4: ULN2803A; SOIC-18W_7.5x11.6mm_P1.27mm
U5: AMS1117-5.0; SOT-223-3_TabPin2

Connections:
+5V: C3.1, C4.1, C5.1, C6.1, R32.1, U1.10, U1.16, U2.14, U3.14, U5.2
+12V: C1.1, C2.1, D1.1, J1.4, J2.4, J3.4, J4.4, K1.1, K2.1, K3.1, K4.1, K5.1, K6.1, K7.1, K8.1, U4.10, U5.3
/AGND: J5.2, J6.2, J7.R, J7.RN, J7.S, J7.SN, J8.R, J8.RN, J8.S, J8.SN, J11.2, J12.2, J13.2, J14.2, J15.2, J16.2, J17.2, J18.2, JP2.1, JP3.2, R1.2, R2.2, R3.2, R4.2, R5.2, R6.2, R7.2, R8.2, R9.2, R10.2, R11.2, R12.2, R13.2, R14.2, R15.2, R16.2
/BYP1: K1.3, K1.10
/BYP2: K2.3, K2.10
/BYP3: K3.3, K3.10
/BYP4: K4.3, K4.10
/BYP5: K5.3, K5.10
/BYP6: K6.3, K6.10
/BYP7: K7.3, K7.10
/BYP8: K8.3, K8.10
/CHASSIS: C7.2, J1.SH, J2.SH, JP3.1, R33.2
/CLK_A: R17.2, R27.1, U2.1
/CLK_J: J1.1, J3.1, R17.1
/CLK_N: U2.2, U2.3
/CLK_O: R22.1, U1.11, U2.4
/CLK_T: J2.1, J4.1, R22.2
/D1: U1.1, U4.8
/D2: U1.2, U4.7
/D3: U1.3, U4.6
/D4: U1.4, U4.5
/D5: U1.5, U4.4
/D6: U1.6, U4.1
/D7: U1.7, U4.2
/D8: U1.15, U4.3
/DATA_A: R18.2, R28.1, U3.1
/DATA_J: J1.3, J3.3, R18.1
/DATA_N: U3.2, U3.3
/DATA_O: U1.14, U3.4
/DRETT_J: J2.6, J4.6, R26.1
/DRET_A: JP1.2, R26.2, R31.1, U3.5
/DRET_J: J1.6, J3.6, R21.2
/DRET_N: U3.6, U3.9
/DRET_O: R21.1, U3.8
/EN_A: R20.2, R30.1, U2.11
/EN_J: J1.8, J3.8, R20.1
/EN_O: R25.1, U2.12
/EN_T: J2.8, J4.8, R25.2
/INTN: J7.TN, JP2.2
/LATCH_A: R19.2, R29.1, U2.5
/LATCH_J: J1.7, J3.7, R19.1
/LATCH_N: U2.6, U2.9
/LATCH_O: R24.1, U1.12, U2.8
/LATCH_T: J2.7, J4.7, R24.2
/LEDA: D2.2, R32.2
/N0: J5.1, J7.T, K1.9
/N1: K1.4, K2.9
/N2: K2.4, K3.9
/N3: K3.4, K4.9
/N4: K4.4, K5.9
/N5: K5.4, K6.9
/N6: K6.4, K7.9
/N7: K7.4, K8.9
/N8: J6.1, J8.T, K8.4
/OE_N: U1.13, U2.10, U2.13
/RET1: J11.3, K1.5, R2.1
/RET2: J12.3, K2.5, R4.1
/RET3: J13.3, K3.5, R6.1
/RET4: J14.3, K4.5, R8.1
/RET5: J15.3, K5.5, R10.1
/RET6: J16.3, K6.5, R12.1
/RET7: J17.3, K7.5, R14.1
/RET8: J18.3, K8.5, R16.1
/RLY1: K1.12, U4.11
/RLY2: K2.12, U4.12
/RLY3: K3.12, U4.13
/RLY4: K4.12, U4.14
/RLY5: K5.12, U4.15
/RLY6: K6.12, U4.18
/RLY7: K7.12, U4.17
/RLY8: K8.12, U4.16
/SEND1: J11.1, K1.8, R1.1
/SEND2: J12.1, K2.8, R3.1
/SEND3: J13.1, K3.8, R5.1
/SEND4: J14.1, K4.8, R7.1
/SEND5: J15.1, K5.8, R9.1
/SEND6: J16.1, K6.8, R11.1
/SEND7: J17.1, K7.8, R13.1
/SEND8: J18.1, K8.8, R15.1
/SER: JP1.1, R23.1, U1.9
/SER_T: J2.3, J4.3, R23.2
GND: C1.2, C2.2, C3.2, C4.2, C5.2, C6.2, C7.1, D1.2, D2.1, J1.2, J1.5, J2.2, J2.5, J3.2, J3.5, J4.2, J4.5, R27.2, R28.2, R29.2, R30.2, R31.2, R33.1, U1.8, U2.7, U3.7, U3.11, U3.13, U4.9, U5.1
